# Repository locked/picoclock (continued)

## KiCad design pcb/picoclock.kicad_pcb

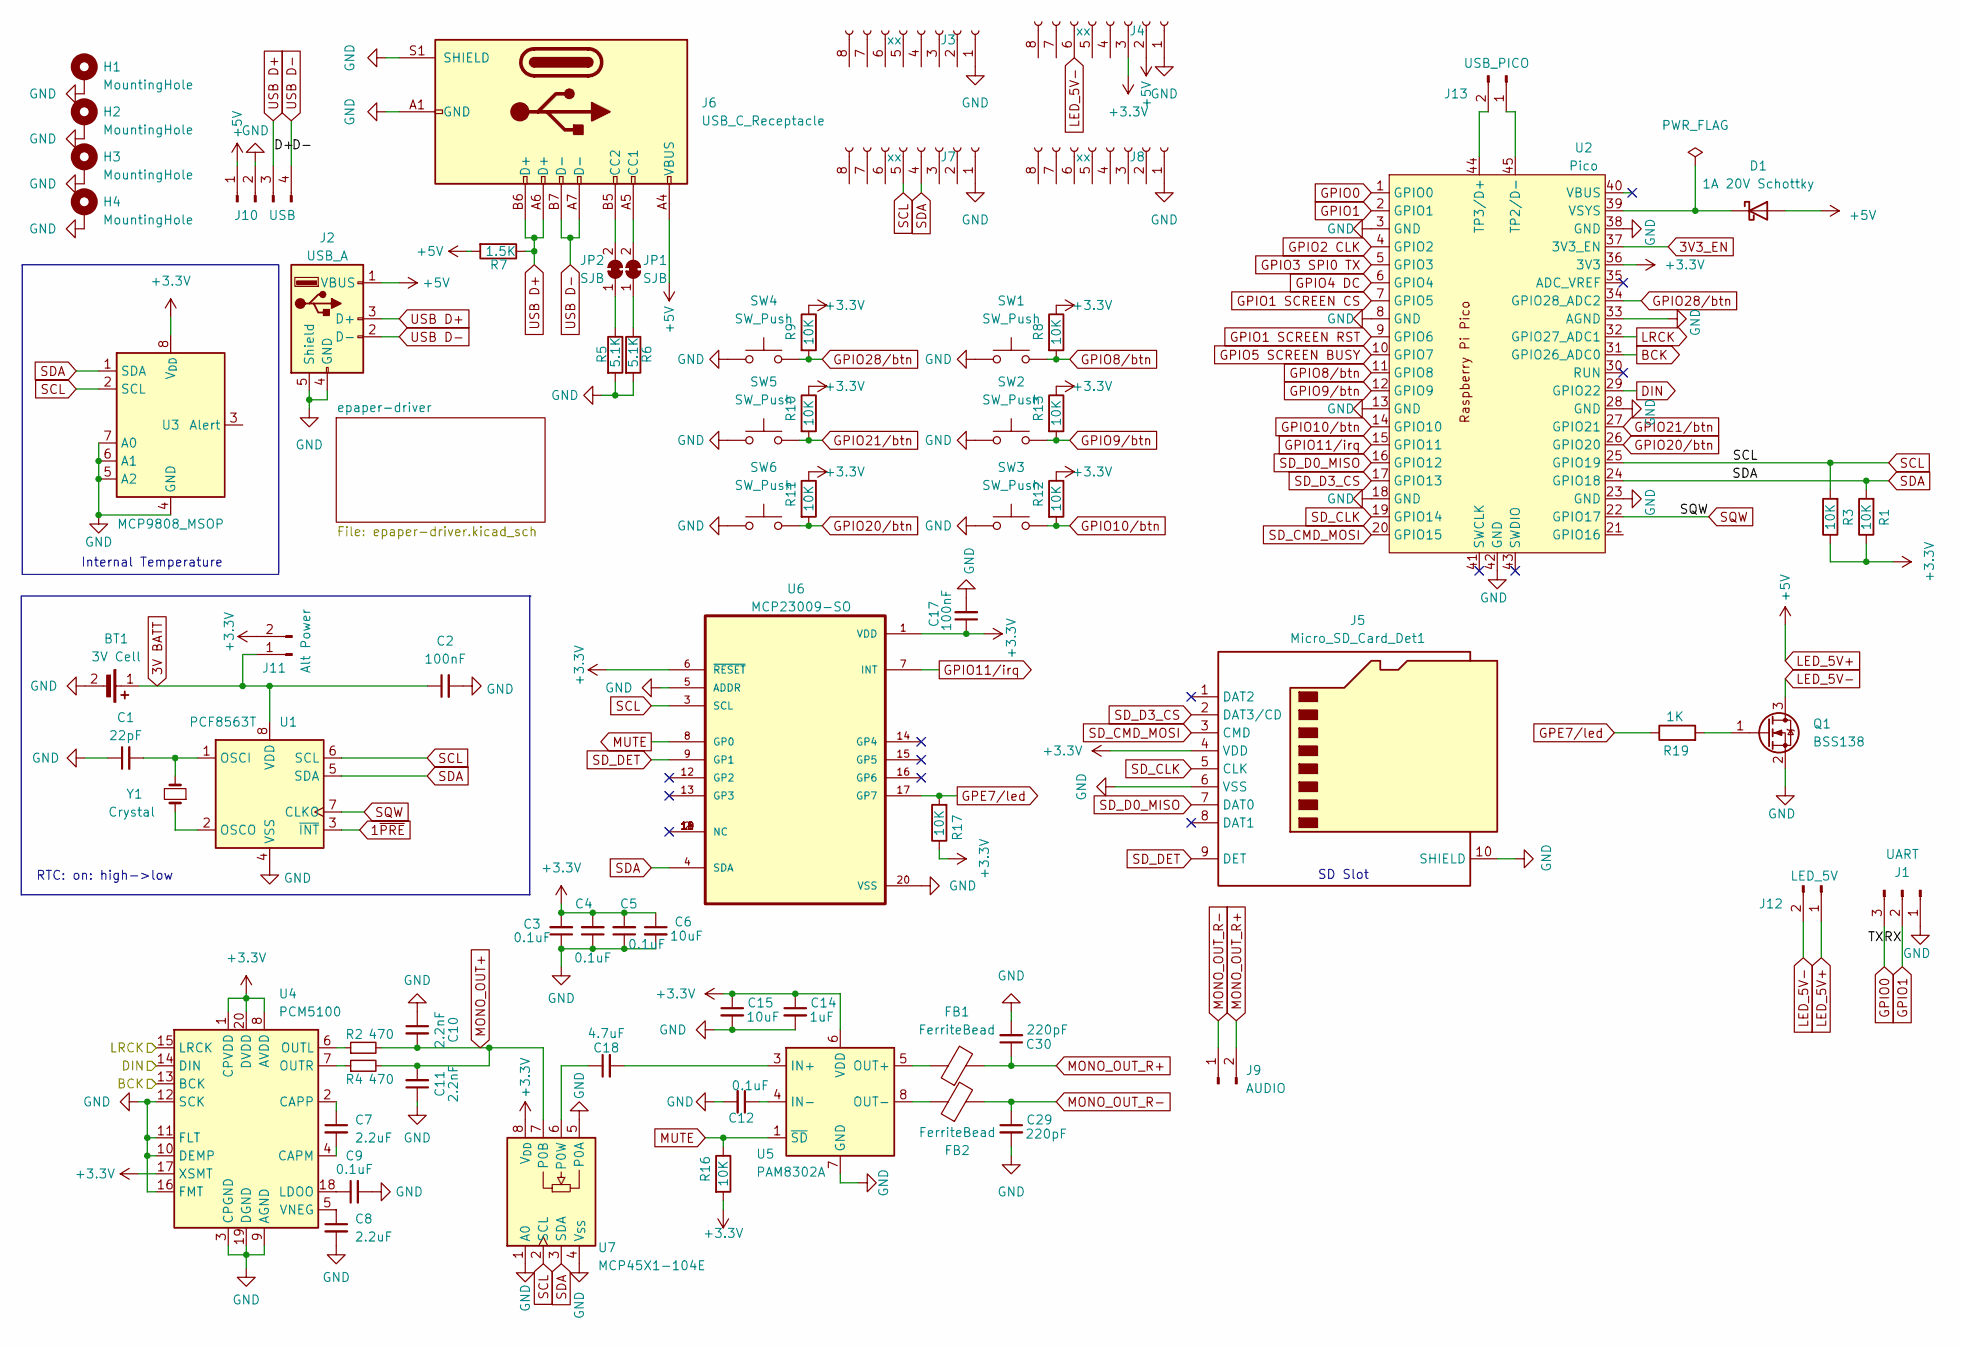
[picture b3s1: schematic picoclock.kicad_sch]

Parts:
BT1: 3V Cell; MPD_BC501SM-TR
C1: 22pF; C_0603_1608Metric; LCSC C1555
C2, C17: 100nF; C_0603_1608Metric; LCSC C1525
C3, C4, C5, C9, C12: 0.1uF; C_0603_1608Metric
C6: 10uF; C_0805_2012Metric
C7: 2.2uF; C_0603_1608Metric
C8: 2.2uF; C_0402_1005Metric
C10, C11: 2.2nF; C_0603_1608Metric
C14: 1uF; C_0603_1608Metric
C15: 10uF; C_0603_1608Metric
C18: 4.7uF; C_0603_1608Metric
C29, C30: 220pF; C_0603_1608Metric
D1: 1A 20V Schottky; D_SOD-123F; LCSC C169527
FB1, FB2: FerriteBead; L_0603_1608Metric
H1, H2, H3, H4: MountingHole; MountingHole_3.2mm_M3_Pad
J1: UART; PinHeader_1x03_P2.54mm_Vertical
J2: USB_A; USB_A_Connfly_DS1095
J3, J4, J7, J8: xx; PinSocket_1x08_P2.54mm_Vertical
J5: Micro_SD_Card_Det1; microSD_HC_Hirose_DM3AT-SF-PEJM5_combined_MSD-4-A
J6: USB_C_Receptacle; USB_C_Receptacle_GCT_USB4105-xx-A_16P_TopMnt_Horizontal
J9: AUDIO; PinHeader_1x02_P2.54mm_Vertical
J10: USB; PinHeader_1x04_P2.54mm_Vertical
J11: Alt Power; PinHeader_1x02_P2.54mm_Vertical
J12: LED_5V; PinHeader_1x02_P2.54mm_Vertical
J13: USB_PICO; PinHeader_1x02_P2.54mm_Vertical
JP1, JP2: SJB; SolderJumper-2_P1.3mm_Bridged_RoundedPad1.0x1.5mm
Q1: BSS138; SOT-23
R1, R3, R8, R9, R10, R11, R12, R13, R16, R17: 10K; R_0603_1608Metric; LCSC C25744
R2, R4: 470; R_0603_1608Metric
R5, R6: 5.1K; R_0603_1608Metric
R7: 1.5K; R_0603_1608Metric
R19: 1K; R_0603_1608Metric; LCSC C25744
SW1, SW2, SW3, SW4, SW5, SW6: SW_Push; SW_SPST_TL3301TG
U1: PCF8563T; SOIC-8_3.9x4.9mm_P1.27mm; LCSC C7440
U2: Pico; RPi_Pico_SMD_TH
U3: MCP9808_MSOP; MSOP-8_3x3mm_P0.65mm; LCSC C129490
U4: PCM5100; TSSOP-20_4.4x6.5mm_P0.65mm
U5: PAM8302A; SOP-8_3.76x4.96mm_P1.27mm
U6: MCP23009-SO; SOP65P780X200-20N; PARTREV C
U7: MCP45X1-104E; MSOP-8_3x3mm_P0.65mm
Y1: Crystal; Crystal_SMD_3215-2Pin_3.2x1.5mm; LCSC C32346

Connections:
1~PRE: U1.3 (~INT)
3V3_EN: U2.37 (3V3_EN)
3V BATT: BT1.1 (+), C2.1, J11.1, U1.8 (VDD)
+3.3V: C3.2, C4.2, C5.2, C6.1, C14.1, C15.1, C17.1, J4.3, J5.4 (VDD), J11.2, R1.1, R3.1, R8.1, R9.1, R10.1, R11.1, R12.1, R13.1, R16.2, R17.1, U2.36 (3V3), U3.8 (V_{DD}), U4.1 (CPVDD), U4.8 (AVDD), U4.17 (XSMT), U4.20 (DVDD), U5.6 (VDD), U6.1 (VDD), U6.6 (~RESET), U7.8 (V_{DD}); also elsewhere on the board
BCK: U2.31 (GPIO26_ADC0), U4.13 (BCK)
DIN: U2.29 (GPIO22), U4.14 (DIN)
GND: BT1.2 (-), C1.1, C2.2, C3.1, C4.1, C5.1, C6.2, C8.2, C9.2, C10.1, C11.1, C12.2, C14.2, C15.2, C17.2, C29.2, C30.2, H1.1, H2.1, H3.1, H4.1, J1.1, J2.4 (GND), J2.5 (Shield), J3.1, J4.1, J5.6 (VSS), J5.10 (SHIELD), J6.A1 (GND), J6.A12 (GND), J6.B1 (GND), J6.B12 (GND), J6.S1 (SHIELD), J7.1, J8.1, J10.2, Q1.2 (S), R5.2, R6.2, SW1.1, SW2.1, SW3.1, SW4.1, SW5.1, SW6.1, U1.4 (VSS), U2.3 (GND), U2.8 (GND), U2.13 (GND), U2.18 (GND), U2.23 (GND), U2.28 (GND), U2.33 (AGND), U2.38 (GND), U2.42 (GND), U3.4 (GND), U3.5 (A2), U3.6 (A1), U3.7 (A0), U4.3 (CPGND), U4.9 (AGND), U4.10 (DEMP), U4.11 (FLT), U4.12 (SCK), U4.16 (FMT), U4.19 (DGND), U5.7 (GND), U6.5 (ADDR), U6.20 (VSS), U7.1 (A0), U7.4 (V_{SS}), U7.5 (P0A); also elsewhere on the board
GPE7/led: R17.2, R19.1, U6.17 (GP7)
GPIO0: J1.3, U2.1 (GPIO0)
GPIO1: J1.2, U2.2 (GPIO1)
GPIO1 SCREEN CS: U2.7 (GPIO5); also elsewhere on the board
GPIO1 SCREEN RST: U2.9 (GPIO6); also elsewhere on the board
GPIO2 CLK: U2.4 (GPIO2); also elsewhere on the board
GPIO3 SPI0 TX: U2.5 (GPIO3); also elsewhere on the board
GPIO4 DC: U2.6 (GPIO4); also elsewhere on the board
GPIO5 SCREEN BUSY: U2.10 (GPIO7); also elsewhere on the board
GPIO8/btn: R8.2, SW1.2, U2.11 (GPIO8)
GPIO9/btn: R13.2, SW2.2, U2.12 (GPIO9)
GPIO10/btn: R12.2, SW3.2, U2.14 (GPIO10)
GPIO11/irq: U2.15 (GPIO11), U6.7 (INT)
GPIO20/btn: R11.2, SW6.2, U2.26 (GPIO20)
GPIO21/btn: R10.2, SW5.2, U2.27 (GPIO21)
GPIO28/btn: R9.2, SW4.2, U2.34 (GPIO28_ADC2)
LED_5V+: D1.2 (A), J2.1 (VBUS), J4.2, J6.A4 (VBUS), J6.A9 (VBUS), J6.B4 (VBUS), J6.B9 (VBUS), J10.1, J12.1, R7.2
LED_5V-: J4.6, J12.2, Q1.3 (D)
LRCK: U2.32 (GPIO27_ADC1), U4.15 (LRCK)
MONO_OUT+: C10.2, C11.2, R2.2, R4.2, U7.7 (P0B)
MONO_OUT_R+: C30.1, FB1.2, J9.2
MONO_OUT_R-: C29.1, FB2.2, J9.1
MUTE: R16.1, U5.1 (~SD), U6.8 (GP0)
unnamed: D1.1 (K), U2.39 (VSYS)
unnamed: J6.A5 (CC1), JP1.2 (B)
unnamed: J6.B5 (CC2), JP2.2 (B)
unnamed: J13.1, U2.45 (TP2/D-)
unnamed: J13.2, U2.44 (TP3/D+)
unnamed: JP1.1 (A), R6.1
unnamed: JP2.1 (A), R5.1
unnamed: Q1.1 (G), R19.2
unnamed: C1.2, U1.1 (OSCI), Y1.2
unnamed: U1.2 (OSCO), Y1.1
unnamed: C7.2, U4.4 (CAPM)
unnamed: C7.1, U4.2 (CAPP)
unnamed: C9.1, U4.18 (LDOO)
unnamed: R2.1, U4.6 (OUTL)
unnamed: R4.1, U4.7 (OUTR)
unnamed: C8.1, U4.5 (VNEG)
unnamed: C18.2, U5.3 (IN+)
unnamed: C12.1, U5.4 (IN-)
unnamed: FB1.1, U5.5 (OUT+)
unnamed: FB2.1, U5.8 (OUT-)
unnamed: C18.1, U7.6 (P0W)
SCL: J7.5, R3.2, U1.6 (SCL), U2.25 (GPIO19), U3.2 (SCL), U6.3 (SCL), U7.2 (SCL)
SDA: J7.4, R1.2, U1.5 (SDA), U2.24 (GPIO18), U3.1 (SDA), U6.4 (SDA), U7.3 (SDA)
SD_CLK: J5.5 (CLK), U2.19 (GPIO14)
SD_CMD_MOSI: J5.3 (CMD), U2.20 (GPIO15)
SD_D0_MISO: J5.7 (DAT0), U2.16 (GPIO12)
SD_D3_CS: J5.2 (DAT3/CD), U2.17 (GPIO13)
SD_DET: J5.9 (DET), U6.9 (GP1)
SQW: U1.7 (CLKO), U2.22 (GPIO17)
USB D+: J2.3 (D+), J6.A6 (D+), J6.B6 (D+), J10.3, R7.1
USB D-: J2.2 (D-), J6.A7 (D-), J6.B7 (D-), J10.4

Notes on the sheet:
SD Slot
Internal Temperature
RTC: on: high->low

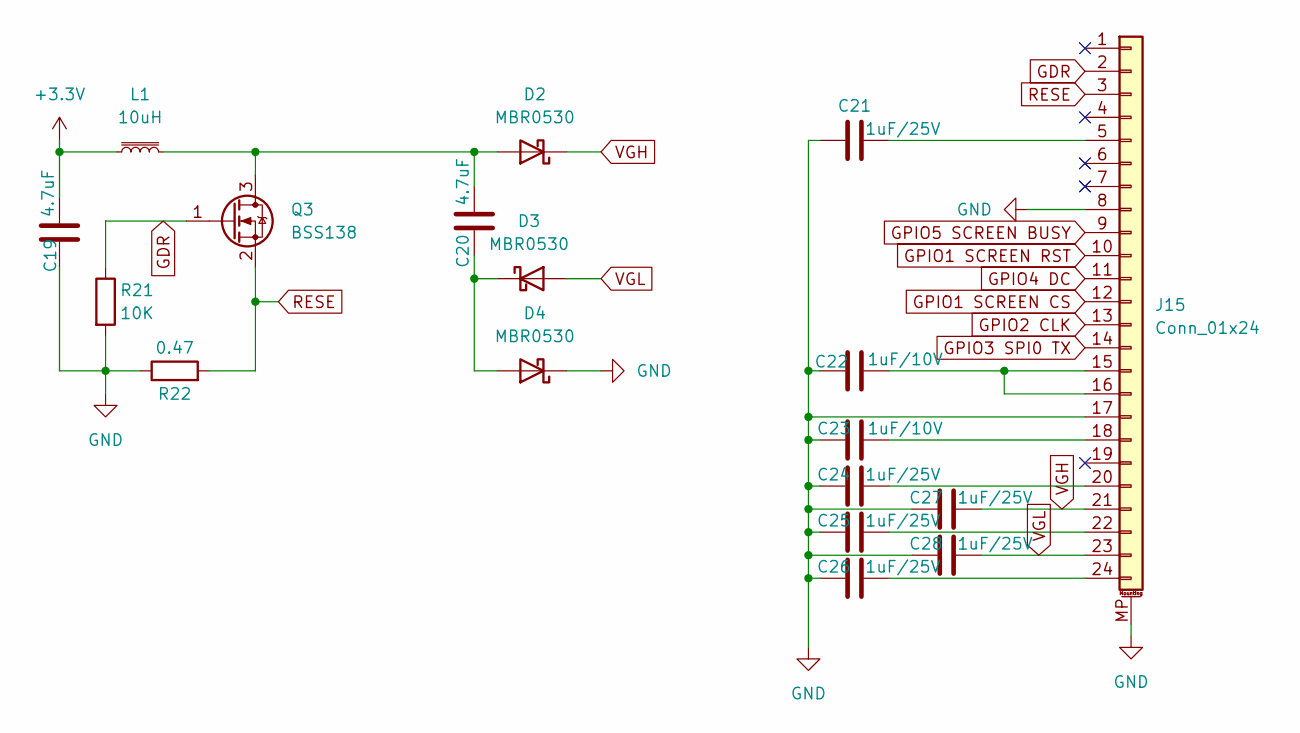
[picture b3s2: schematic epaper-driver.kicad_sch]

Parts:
C19, C20: 4.7uF; C_0603_1608Metric
C21, C24, C25, C26, C27, C28: 1uF/25V; C_0603_1608Metric
C22, C23: 1uF/10V; C_0603_1608Metric
D2, D3, D4: MBR0530; D_SOD-123
J15: Conn_01x24; Hirose_FH12-24S-0.5SH_1x24-1MP_P0.50mm_Horizontal
L1: 10uH; L_TDK_NLV32_3.2x2.5mm
Q3: BSS138; SOT-23-3
R21: 10K; R_0603_1608Metric
R22: 0.47; R_0603_1608Metric

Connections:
+3.3V: C19.1, L1.1; also elsewhere on the board
GDR: J15.2, Q3.1 (G), R21.1
GND: C19.2, C21.2, C22.2, C23.2, C24.2, C25.2, C26.2, C27.2, C28.2, D4.1 (K), J15.8, J15.17, J15.MP (MountPin), R21.2, R22.1; also elsewhere on the board
GPIO1 SCREEN CS: J15.12; also elsewhere on the board
GPIO1 SCREEN RST: J15.10; also elsewhere on the board
GPIO2 CLK: J15.13; also elsewhere on the board
GPIO3 SPI0 TX: J15.14; also elsewhere on the board
GPIO4 DC: J15.11; also elsewhere on the board
GPIO5 SCREEN BUSY: J15.9; also elsewhere on the board
unnamed: C20.1, D2.2 (A), L1.2, Q3.3 (D)
unnamed: C20.2, D3.1 (K), D4.2 (A)
unnamed: C21.1, J15.5
unnamed: C22.1, J15.15, J15.16
unnamed: C23.1, J15.18
unnamed: C24.1, J15.20
unnamed: C25.1, J15.22
unnamed: C26.1, J15.24
RESE: J15.3, Q3.2 (S), R22.2
VGH: C27.1, D2.1 (K), J15.21
VGL: C28.1, D3.2 (A), J15.23

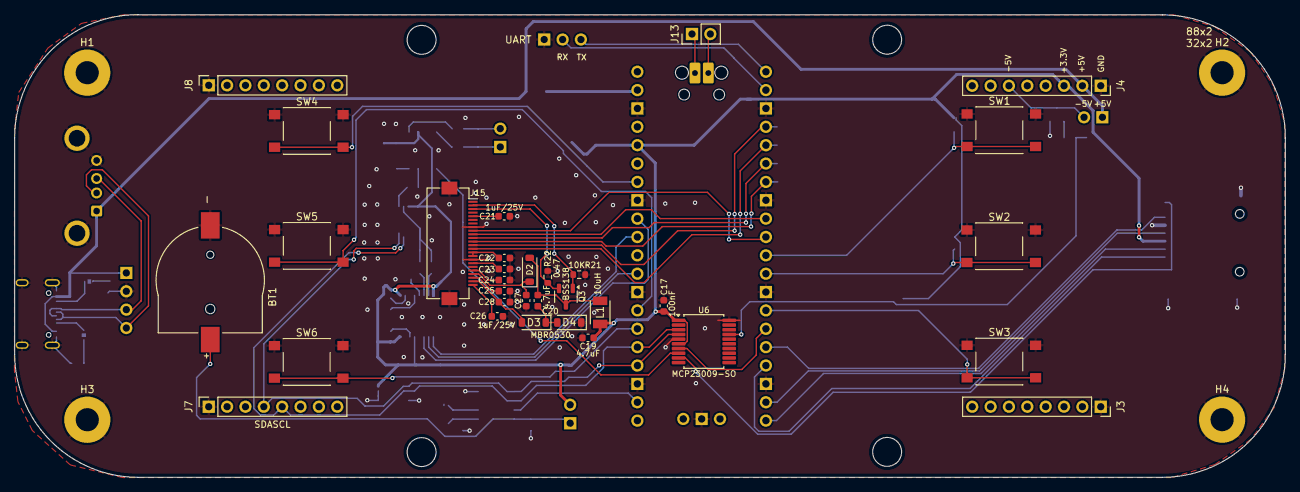
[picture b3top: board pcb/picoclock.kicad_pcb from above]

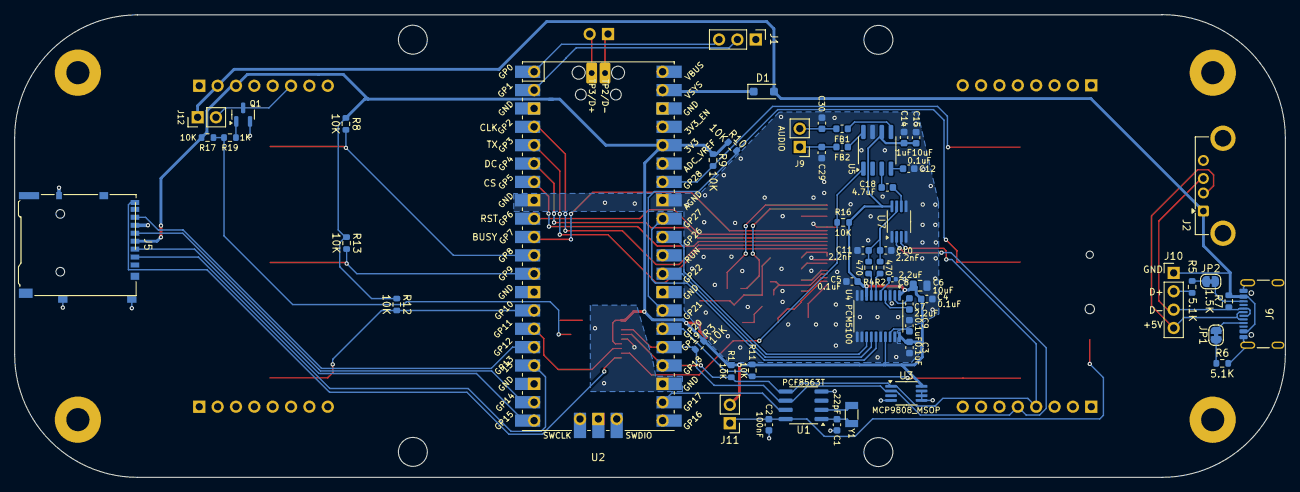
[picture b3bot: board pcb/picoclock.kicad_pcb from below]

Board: 2 copper layers, 175.7 x 64.0 mm, 90 parts (54 on the bottom side), 71 nets.

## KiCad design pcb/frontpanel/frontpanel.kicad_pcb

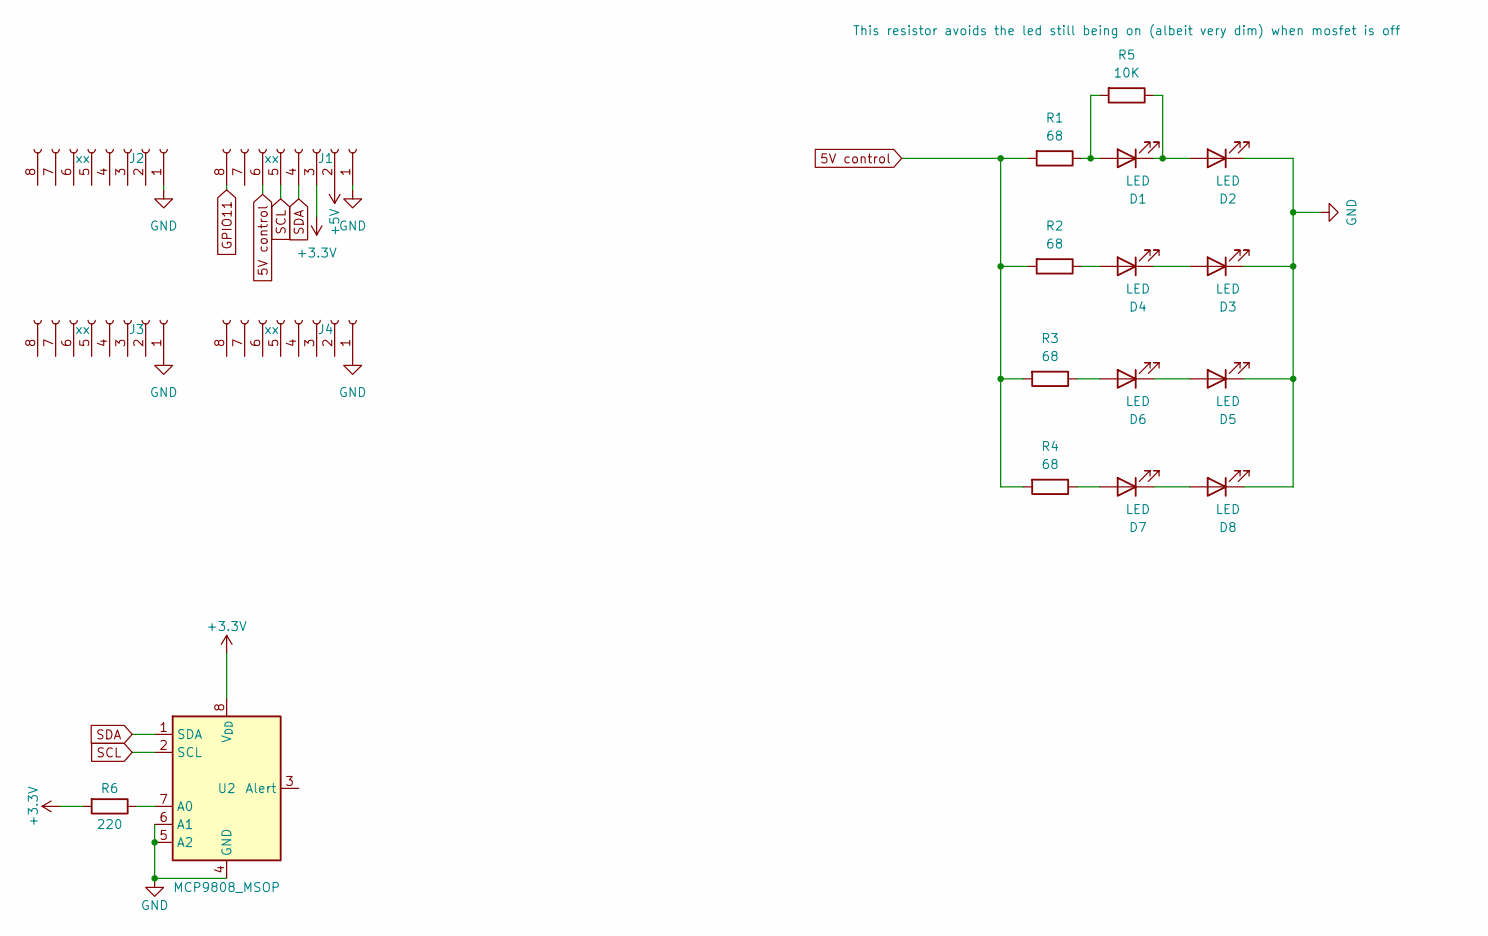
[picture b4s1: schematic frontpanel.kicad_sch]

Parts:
D1, D2, D3, D4, D5, D6, D7, D8: LED; LED_0805_2012Metric
J1, J2, J3, J4: xx; PinSocket_1x08_P2.54mm_Vertical_SMD_Pin1Left
R1, R2, R3, R4: 68; R_0603_1608Metric
R5: 10K; R_0603_1608Metric
R6: 220; R_0603_1608Metric
U2: MCP9808_MSOP; MSOP-8_3x3mm_P0.65mm; LCSC C129490

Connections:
5V control: J1.6, R1.2, R2.2, R3.2, R4.2
+3.3V: J1.3, R6.2, U2.8 (V_{DD})
+5V: J1.2
GND: D2.1 (K), D3.1 (K), D5.1 (K), D8.1 (K), J1.1, J2.1, J3.1, J4.1, U2.4 (GND), U2.5 (A2), U2.6 (A1)
GPIO11: J1.8
unnamed: D1.2 (A), R1.1, R5.2
unnamed: D1.1 (K), D2.2 (A), R5.1
unnamed: D3.2 (A), D4.1 (K)
unnamed: D4.2 (A), R2.1
unnamed: D5.2 (A), D6.1 (K)
unnamed: D6.2 (A), R3.1
unnamed: D7.2 (A), R4.1
unnamed: D7.1 (K), D8.2 (A)
unnamed: R6.1, U2.7 (A0)
SCL: J1.5, U2.2 (SCL)
SDA: J1.4, U2.1 (SDA)

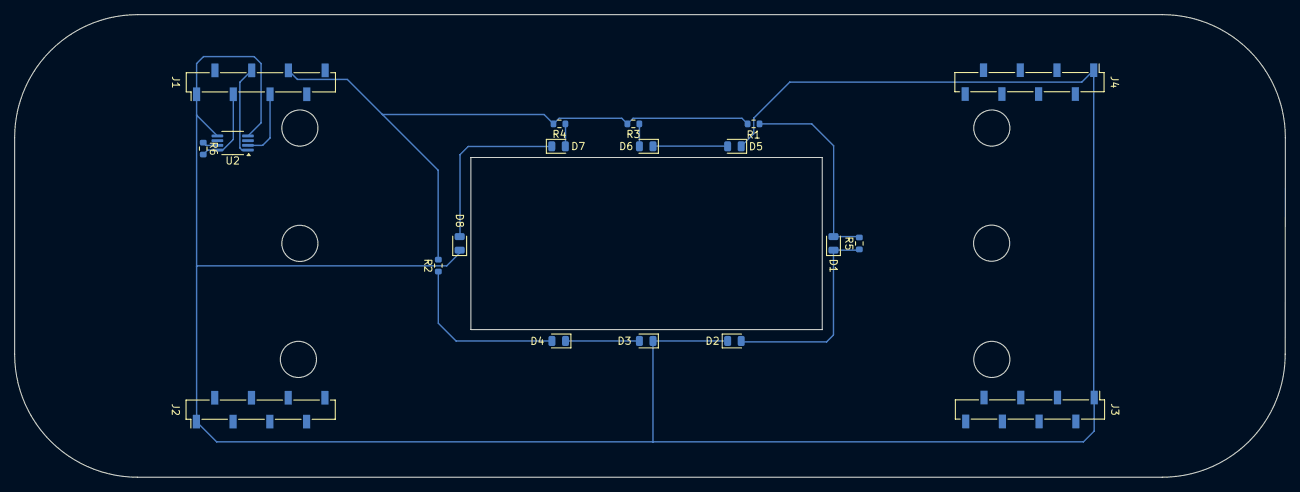
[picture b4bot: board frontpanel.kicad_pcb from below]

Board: 2 copper layers, 175.7 x 63.9 mm, 19 parts (19 on the bottom side), 14 nets.

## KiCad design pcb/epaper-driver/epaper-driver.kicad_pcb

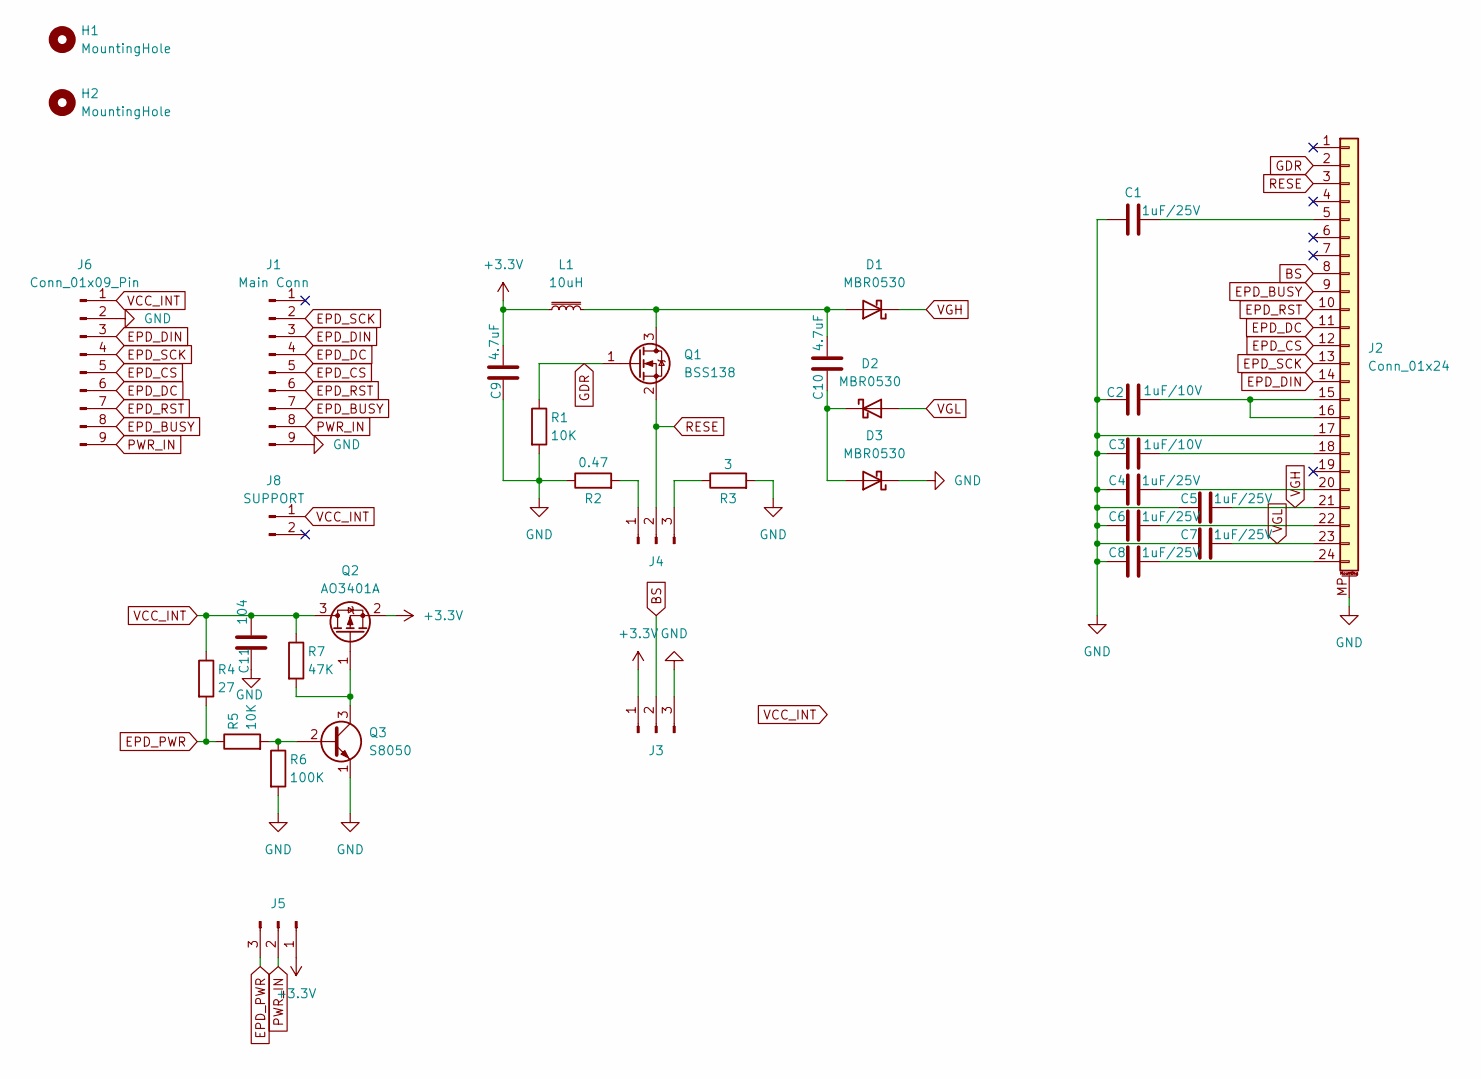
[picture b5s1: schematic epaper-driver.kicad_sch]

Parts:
C1, C4, C5, C6, C7, C8: 1uF/25V; C_0603_1608Metric
C2, C3: 1uF/10V; C_0603_1608Metric
C9, C10: 4.7uF; C_0603_1608Metric
C11: 104; C_0603_1608Metric
D1, D2, D3: MBR0530; D_SOD-123
H1, H2: MountingHole; MountingHole_2.2mm_M2
J1: Main Conn; PinHeader_1x09_P2.54mm_Vertical
J2: Conn_01x24; Hirose_FH12-24S-0.5SH_1x24-1MP_P0.50mm_Horizontal
J3, J4: Conn_01x03_Pin; PinHeader_1x03_P1.00mm_Vertical
J5: Conn_01x03_Pin; PinHeader_1x03_P2.54mm_Vertical
J6: Conn_01x09_Pin
J8: SUPPORT; PinHeader_1x02_P2.54mm_Vertical
L1: 10uH; L_TDK_NLV32_3.2x2.5mm
Q1: BSS138; SOT-23-3
Q2: AO3401A; SOT-23-3
Q3: S8050; SOT-23-3
R1, R5: 10K; R_0603_1608Metric
R2: 0.47; R_0603_1608Metric
R3: 3; R_0603_1608Metric
R4: 27; R_0603_1608Metric
R6: 100K; R_0603_1608Metric
R7: 47K; R_0603_1608Metric

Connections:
+3.3V: C9.1, J3.1, J5.1, L1.1, Q2.2 (S)
BS: J2.8, J3.2
EPD_BUSY: J1.7, J2.9, J6.8
EPD_CS: J1.5, J2.12, J6.5
EPD_DC: J1.4, J2.11, J6.6
EPD_DIN: J1.3, J2.14, J6.3
EPD_PWR: J5.3, R4.2, R5.1
EPD_RST: J1.6, J2.10, J6.7
EPD_SCK: J1.2, J2.13, J6.4
GDR: J2.2, Q1.1 (G), R1.1
GND: C1.2, C2.2, C3.2, C4.2, C5.2, C6.2, C7.2, C8.2, C9.2, C11.2, D3.1 (K), J1.9, J2.17, J2.MP (MountPin), J3.3, J6.2, Q3.1 (E), R1.2, R2.1, R3.2, R6.2
unnamed: C10.1, D1.2 (A), L1.2, Q1.3 (D)
unnamed: C10.2, D2.1 (K), D3.2 (A)
unnamed: C1.1, J2.5
unnamed: C2.1, J2.15, J2.16
unnamed: C3.1, J2.18
unnamed: C4.1, J2.20
unnamed: C6.1, J2.22
unnamed: C8.1, J2.24
unnamed: J4.1, R2.2
unnamed: J4.3, R3.1
unnamed: Q2.1 (G), Q3.3 (C), R7.2
unnamed: Q3.2 (B), R5.2, R6.1
PWR_IN: J1.8, J5.2, J6.9
RESE: J2.3, J4.2, Q1.2 (S)
VCC_INT: C11.1, J6.1, J8.1, Q2.3 (D), R4.1, R7.1
VGH: C5.1, D1.1 (K), J2.21
VGL: C7.1, D2.2 (A), J2.23

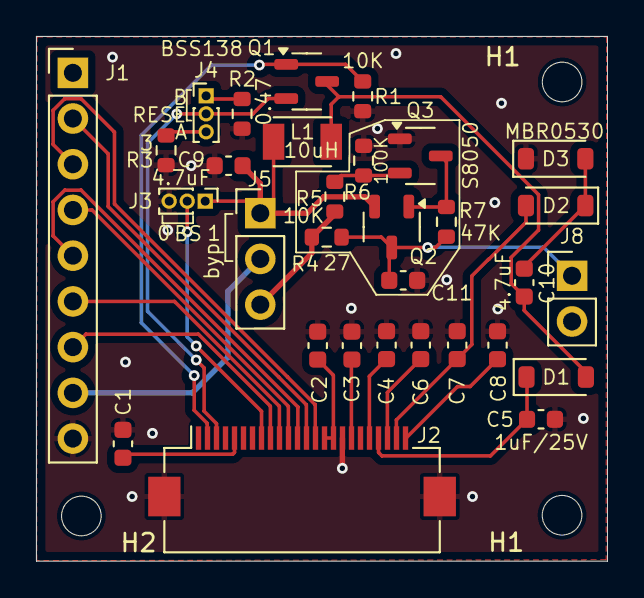
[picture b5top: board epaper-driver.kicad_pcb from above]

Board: 2 copper layers, 31.7 x 29.2 mm, 34 parts (0 on the bottom side), 28 nets.

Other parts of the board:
H1#2: MountingHole; MountingHole_2.2mm_M2

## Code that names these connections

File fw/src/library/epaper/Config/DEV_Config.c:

/*****************************************************************************
* | File      	:   DEV_Config.c
* | Author      :   Waveshare team
* | Function    :   Hardware underlying interface
* | Info        :
*----------------
* |	This version:   V3.0
* | Date        :   2019-07-31
* | Info        :   
#
# Permission is hereby granted, free of charge, to any person obtaining a copy
# of this software and associated documnetation files (the "Software"), to deal
# in the Software without restriction, including without limitation the rights
# to use, copy, modify, merge, publish, distribute, sublicense, and/or sell
# copies of theex Software, and to permit persons to  whom the Software is
# furished to do so, subject to the following conditions:
#
# The above copyright notice and this permission notice shall be included in
# all copies or substantial portions of the Software.
#
# THE SOFTWARE IS PROVIDED "AS IS", WITHOUT WARRANTY OF ANY KIND, EXPRESS OR
# IMPLIED, INCLUDING BUT NOT LIMITED TO THE WARRANTIES OF MERCHANTABILITY,
# FITNESS OR A PARTICULAR PURPOSE AND NONINFRINGEMENT. IN NO EVENT SHALL THE
# AUTHORS OR COPYRIGHT HOLDERS BE LIABLE FOR ANY CLAIM, DAMAGES OR OTHER
# LIABILITY WHETHER IN AN ACTION OF CONTRACT, TORT OR OTHERWISE, ARISING FROM,
# OUT OF OR IN CONNECTION WITH THE SOFTWARE OR THE USE OR OTHER DEALINGS IN
# THE SOFTWARE.
#
******************************************************************************/
#include "DEV_Config.h"

#define SPI_PORT spi0

/**
 * GPIO
**/
int EPD_RST_PIN;
int EPD_DC_PIN;
int EPD_CS_PIN;
int EPD_BUSY_PIN;
int EPD_CLK_PIN;
int EPD_MOSI_PIN;

/**
 * GPIO read and write
**/
void DEV_Digital_Write(UWORD Pin, UBYTE Value)
{
	gpio_put(Pin, Value);
}

UBYTE DEV_Digital_Read(UWORD Pin)
{
	return gpio_get(Pin);
}

/**
 * SPI
**/
void DEV_SPI_WriteByte(uint8_t Value)
{
    spi_write_blocking(SPI_PORT, &Value, 1);
}

void DEV_SPI_Write_nByte(uint8_t *pData, uint32_t Len)
{
    spi_write_blocking(SPI_PORT, pData, Len);
}

/**
 * GPIO Mode
**/
void DEV_GPIO_Mode(UWORD Pin, UWORD Mode)
{
    gpio_init(Pin);
	if(Mode == 0 || Mode == GPIO_IN) {
		gpio_set_dir(Pin, GPIO_IN);
	} else {
		gpio_set_dir(Pin, GPIO_OUT);
	}
}

/**
 * delay x ms
**/
void DEV_Delay_ms(UDOUBLE xms)
{
	sleep_ms(xms);
}

void DEV_GPIO_Init(void)
{
	/*
	EPD_RST_PIN     = 12;
	EPD_DC_PIN      = 8;
	EPD_BUSY_PIN    = 13;
	
	EPD_CS_PIN      = 9;
	EPD_CLK_PIN		= 10;
	EPD_MOSI_PIN	= 11;
	*/

	EPD_RST_PIN     = 6;
	EPD_DC_PIN      = 4; //28;
	EPD_BUSY_PIN    = 7;

	EPD_CS_PIN      = 5;
	EPD_CLK_PIN		= 2;
	EPD_MOSI_PIN	= 3;

	DEV_GPIO_Mode(EPD_RST_PIN, 1);
	DEV_GPIO_Mode(EPD_DC_PIN, 1);
	DEV_GPIO_Mode(EPD_CS_PIN, 1);
	DEV_GPIO_Mode(EPD_BUSY_PIN, 0);

	DEV_Digital_Write(EPD_CS_PIN, 1);
}
/******************************************************************************
function:	Module Initialize, the library and initialize the pins, SPI protocol
parameter:
Info:
******************************************************************************/
UBYTE DEV_Module_Init(void) {
	// GPIO Config
	DEV_GPIO_Init();

	spi_init(SPI_PORT, 4000 * 1000);
	gpio_set_function(EPD_CLK_PIN, GPIO_FUNC_SPI);
	gpio_set_function(EPD_MOSI_PIN, GPIO_FUNC_SPI);

	printf("DEV_Module_Init OK \r\n");
	return 0;
}

/******************************************************************************
function:	Module exits, closes SPI and BCM2835 library
parameter:
Info:
******************************************************************************/
void DEV_Module_Exit(void)
{

}

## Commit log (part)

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2024-06-09 pcb + 3d
2024-06-16 update case+pcb
2024-06-16 add frontpanel PCB, update back PCB
2024-07-20 [pcb] update
2024-07-27 [pcb] fix epaper hat position, fix GPIO, add labels
2024-07-27 [pcb] add PWR from epaper hat
2024-07-27 [fw] add first version, *non functional*
    This is based on the open-story-teller project located
    here: https://github.com/arabine/open-story-teller
2024-07-27 [fw] add wifi support (kinda)
2024-07-28 [fw] add melody on btn 3
2024-07-28 [fw] move stuff around, add alarm functionality
2024-07-30 [pcb] update frontpanel (mostly, leds)
2024-07-30 [fw] minor cleanup, sound on buttons
2024-08-03 [pcb] fix frontpanel pcb LEDs + connexion to main pcb
2024-08-11 [pcb] add capybara logo
2024-08-11 [fw] add mcp9808 temperature lib, beter handling of wifi connexion failure
2024-08-11 [fw] add pcf8563 library + use it
    No longer connect to wifi at every boot to
    get the date/time: need to add some logic to
    periodically check
2024-08-11 very basic screen handling
2024-08-11 [fw] do not partial refresh on clear + fix left btn
2024-08-15 [pcb] use optocoupler in frontpanel
2024-08-15 [fw] better handling of button
2024-08-15 [fw] add script to convert gif to c struct
2024-08-17 [fw] add icons
2024-08-17 [fw] fix small bugs
2024-08-17 [3d] add button (needs to adjust dimensions)
2024-08-18 [fw] add tinyhttp and use it to sync using http instead of raw tcp + cleanup
    Library from: https://github.com/mendsley/tinyhttp
2024-08-18 [fw] add weather from api
2024-08-18 [api] add example
2024-08-18 [pcb] add PWM out
2024-08-18 add basic README
2024-08-18 improve readmes
2024-08-18 [readme] add api folder
2024-08-18 [readme] style
2024-08-18 [api] improve to use config file
2024-08-23 [3d] increase btn slot size
2024-08-25 [case] fix usb position, add internal support
2024-08-25 [pcb] fix PCM5100 layout, AVDD, improvements
2024-08-25 [fw] add icons source
2024-09-01 [pcb] add sdcard: had to move PCM5100, other
2024-09-01 [3d] button: 2.4 and 2.5 sizes ok
2024-09-01 [audio] i2s works when using example method, still not with pio
2024-09-01 [build] move files to library/, add missing files
2024-09-01 [build] comsetic change
2024-09-01 [fw] handle multiple alarms (get/store in flash) + fixes
2024-09-02 [fw] re-enable PWM sound
2024-09-04 [fw] cleanup + disable flash write causing qor_sleep to hang
2024-09-07 display alarms in main screen, disable flash read
2024-09-08 [api] multi alarms json
2024-09-08 [pcb] add sdcard, audio amplifier
2024-09-08 add sdcard support
2024-09-08 [sdcard] add sdcard lib + ff
2024-09-29 [pcb] add epaper driver board
2024-10-02 [3d] small changes to case
2024-10-02 [pcb] update/fixes for #prod2
2024-10-05 [3d] add stronger support following jlcpcb review
2024-10-05 [pcb] CYW43439 module board
    Missing antenna, needs tons of review
2024-10-23 [pcb] epaper-driver: mostly silkscreen size changes
2024-10-25 [pcb] move rev2 into dedicated folder + start new rev
2024-10-26 [pcb] audio circuit fixes
2024-10-27 [fw] add mcp23009 library
2024-10-27 [fw] add mcp4652 (digital potentiometer) library
2024-10-27 [fw] audio rework: use digital pot (mcp4652), enable i2s with dma/pio
2024-11-13 [pcb] CYW43439: add 4 layers version
2024-11-13 [pcb] rename 2 layers version to CYW43439-2L
2024-11-13 [pcb] re-organize folders
2024-11-16 [fw] alarm with i2s/wav, better alarms display
2024-11-19 [fw] alarm fixes
2024-11-20 [core] re-organize a bit
2024-12-03 [pcb] fixes for mcp23009 (bad footprint)
2024-12-03 [wifi] cleanup library
2024-12-03 [pcb] cleanup
2024-12-15 [mcp23009] add more functions, fixes for PCBv2
2024-12-15 [pcb] add pullup resistor for MCP23009
2024-12-24 [fw] pcf8563: fct to set i2c, var to set volume, param for alarm chime
2025-01-18 [3d] update front screen holder
2025-01-18 [pcb] update 4 layer wifi test board
2025-01-18 [pcb] update symbol for MCP4652
2025-01-18 [pcb] move battery holder, other small tweaks
2025-02-13 [fw] add 4651 support, tweaks&fixes
2025-02-15 [fw] big update: config support, split code
2025-02-15 [fw] remove unused imports/variables, cleanup
2025-02-24 reliability: avoid crash if mcp23009 is not found
2025-02-24 [readme] update with simple build instructions
2025-03-05 [fw] do not crash on mp23009 not available
2025-03-05 [3d] add front-v1
2025-03-08 [pcb] mono audio, combined sdcard footprint
2025-03-15 [3d] revamp of screen support (front), add panel (wip), fixes on main case
2025-03-19 [3d] first usable release of panel, add button stl
2025-03-21 [3d] update panel
2025-05-18 [pcb] add USB-A
2025-05-18 [pcb] move symbols into common lib, add pogo pins on pico
2025-05-18 [fw] support for "V4B" screen + add reboot everyday with watchdog
2025-06-08 [case] add USB-A port
2025-06-08 [pcb] adjust pcb outline
2025-08-31 [CYW43439] fix VDDBAT/LDO_IN short circuited, others
2025-11-01 [pcb-mini] add ESP32, RM2, route most things
2025-11-01 [pcb-mini] fix warnings/errors
2025-11-09 [3d] add mini case
2025-11-09 [3d] add screen holder for mini case
2025-11-11 [mini] add pin for screen holder in pcb + 3d
2025-11-11 [3d] add stl for front/screenholder/pcb
2025-11-14 [3d] fix io ports, add back case
2025-11-15 [pcb-mini] add proper audio jack
2025-11-16 [mini] fix I/O positions, add jack in case
2025-11-16 [pcb] mini: audio shut internal speaker when hack is connected
2025-11-17 [3d] mini: several minor tweaks
2025-11-18 [3d] mini: improve back joint
2025-11-18 [pcb] add leds
2025-11-20 [3d] mini: improvements
    - [done] increase screw hole size
    - [done] increase depth for back case bolts
    - [done] add hole under for speaker screws
    - [done] move speaker closer to wall by 4mm
2025-11-23 [3d] mini: reduce thickness to 1.5, decrease bolt hole diameter
2025-11-23 [3d] mini: adjust screen pin
2025-11-23 [pcb] mini: many silkscreen fixes
2025-11-25 [3d] mini: fix screw pos
2025-11-29 [pcb] mini: add RGB leds
2025-11-30 [pcb] mini: fix I2S switch footprint, many small tweaks
2025-11-30 [3d] mini: fix front, add prod release v6
2025-12-01 [3d] mini: add round speaker support
2025-12-02 [pcb] mini: add ENS160 gaz sensor
2025-12-06 [pcb] mini: add debug port, improve/fix traces
2025-12-07 [pcb] mini: cleanup schematic, fix 3.3v zone
2025-12-13 [pcb] mini: add/fix LCSC refs
2026-01-08 add basic support for new "mini" pcb
2026-01-09 [fw] update GPIO for mini pcb
2026-01-09 [fw] fixes for pcb mini
2026-01-11 [audio] add custom board, basic I2S/DMA support
2026-01-13 [audio] add digital pot (mcp4551) lib
2026-01-14 [3d-mini] wip on fixing joint between back and front
2026-01-14 [case] fix pcb support
2026-01-14 [fw] fix alarm on mini pcb
2026-01-14 [fw] fix indents
2026-01-14 [fw] fix or remove comments
2026-01-15 [3d] mini: fix back+front + add v7 prod
2026-01-15 [3d] mini: add button
2026-01-15 [3d] mini: update button
2026-01-15 [fw] add 74LS157 support, add skeleton of LP5817 led controller lib
2026-01-15 [fw] lp5817: add enable/set_dc (non functional)
2026-01-16 [pcb] mini: fix audio connector, resistor on 74LS157
2026-01-16 [pcb] mini: add ENS160 symbol/footprint
2026-01-17 [3d] mini: fix sdcard+usb-c depth, deeper screw holes
2026-01-17 [pcb] mini: RGB led footprint fixes
2026-01-17 [fw] add (very) basic README
2026-01-20 [fw] fix wifi crash on core0, reduce calls to pcf8563, cleanup
2026-01-20 [pcb] mini: tweaks
2026-01-21 [3d] mini small adjustment + remove large speaker
2026-01-29 [fw] dump i2c bus scan at startup
2026-01-30 [fw] fix ens160 lib
2026-01-30 [pcb] mini: show silkscreen of ens160 dc-dc converter
2026-01-31 [fw] add circularBuffer lib, put metrics in it, add metrics screen
2026-01-31 [pcb] mini: RTC: add diods, wire INT. fix 74LS chip footprint
2026-02-01 [fw] fix red led, send metrics to server
2026-02-04 [fw] add watchdog update in wifi code path, add 'uptime' in sync
2026-02-05 [fw] add json-maker lib
2026-02-07 [fw] add ESP32 UART communication + arduino code
2026-02-08 [esp32] init UART after to give esp32 time to boot
2026-02-08 [esp32] add README, pre-built binaries
2026-02-08 [pcb] mini: move boot btn, add silkscreen, add con for ESP32 UART
2026-02-11 [sdcard] use unix file format, remove debug_printf()
2026-02-11 [fw] add senseair S88 support
2026-02-12 [fw] fixes for alarm screen, remove logs
2026-02-14 [pcb] mini: add senseair schema+footprint
2026-02-15 [fw] add/improve logs
2026-02-15 [pcb] mini: add SHT40 + senseair S88 connectors
2026-02-16 [fw] add RGB stuff
2026-02-17 [3d] mini: put speaker on bottom, add air vents
2026-02-17 [pcb] mini: move audio into dedicated sheet
2026-02-17 [pcb] mini: add STCC4 and SCD41
2026-02-18 [fw] better debug screen for RGB leds
2026-03-01 [fw] add sensirion scd43+stcc4 co2 sensors
    also trigger audio via shared variable so
    that it runs on core 0
2026-03-04 [fw] auto detect present hw, improve logs, improve metrics sending
2026-03-04 [fw] improve sensirion library
2026-03-04 [3d] mini: add btn for short pusher, improve normal one
2026-03-04 [pcb] mini: add decoupling caps, improve power path of screen
2026-03-08 [fw] replace i2c_read_blocking() with i2c_read_timeout_us(), add logs
2026-03-08 [fw] fix stcc4 recv buffer size
2026-03-08 [fw] remove more ost_ prefix
2026-03-08 [fw] enable sd card detection
2026-03-08 [fw] disable gpio to detect sd card, not working
2026-03-10 [fw] add free mem in metrics, cleanup sensirion lib
2026-03-10 [3d] mini: improve shortbase btn
2026-03-14 [pcb] fix SD card detection (add pullup) + improve footprint
2026-03-14 [pcb] mini: cleanup main sheet
2026-03-20 [fw] very hackish way to enable BT
2026-03-20 [fw] add btctrl lib
2026-03-21 [fw] improve icons, UI
2026-04-05 [fw] add base file download and write to SD
2026-04-05 [fw] small fix * debug for dl
2026-04-06 [fw] quick fix for file dl, start OTA work (not working)
2026-04-06 [fw] add http parsing when downloading file
2026-04-11 [fw] read uf2 file from SD and flash
2026-04-11 [fw] working fw update
2026-04-11 [fw] fw update improvements
2026-04-11 [fw] reduce wifi recv log
2026-04-11 [fw] add size check, reduce binary size
2026-04-11 [fw] try to improve reboot
2026-04-12 [stcc] fix buffer length to account for crc
2026-04-14 [build] cleanup CMakeLists.txt
2026-04-16 [fw] dynamically enable UART or not (depends on S88 presence)
2026-04-28 [case] replace long holes by screw inserts
2026-05-03 [case] remove sharp angles
2026-05-04 [case] add case-front and screen holder v10
2026-05-05 [case] add large speaker
2026-05-15 [3d] screen holder: add borders, increase guideline size
2026-05-18 [3d] increase light shade width
2026-05-18 [3d] v13 of screen holder
2026-05-20 [small fixes, v13-3
2026-06-01 [fw] try something to fix intermittent reboot (prob. not working)
2026-06-01 Revert "[fw] try something to fix intermittent reboot (prob. not working)"
    This reverts commit dceef1907c1242770b09cc4d0c5dfdcd7c0f2485.
2026-06-02 [fw] tentative fix (prob. again not working)
2026-06-02 [fw] more tentative fix
2026-06-02 [fw] continuing tentative fixes ^^
2026-06-02 [fw] another tentative + log
2026-06-02 [fw] yet another
2026-06-02 [fw] again
2026-06-02 [fw] fix declaration
2026-06-02 [fw] try stuff
2026-06-02 [fw] try fixing reboot
2026-06-02 [fw] more debug info
2026-06-06 Revert "[fw] try fixing reboot"
    This reverts commit 09a80e802b240961289400ea98ec385455671d0f.
2026-06-06 Revert "[fw] fix declaration"
    This reverts commit 45807112af9c48a4d8d5033e44f841035b88c744.
2026-06-06 Revert "[fw] try stuff"
    This reverts commit 37b781d900e8321c22fd7430398c04eb2d7bc050.
2026-06-06 Revert "[fw] yet another"
    This reverts commit d045a6d5a4ecdb3f40a68f52f540c0d49cae3cba.
2026-06-06 Revert "[fw] again"
    This reverts commit 3096d6e23442766ade29f0885af1c3d3f91fe32f.
2026-06-06 Revert "[fw] add debug"
    This reverts commit 3574517efb9896600bab4d726906962daf220eb2.
2026-06-06 Revert "[fw] another tentative + log"
    This reverts commit 6b8f92f8c7ca5fee219c7c3027469de01f9fd834.
2026-06-06 Revert "[fw] tentative fix (prob. again not working)"
    This reverts commit 2324c3e6f716d66b9156ddabed7a2ffb54288037.
2026-06-06 Revert "[fw] more tentative fix"
    This reverts commit ee65c05ee418b42029c636d06fadf742fb6254fc.
2026-06-06 Reapply "[fw] try something to fix intermittent reboot (prob. not working)"
    This reverts commit d495af2c396d337e4e1601c5f01f60f7c41184f6.
